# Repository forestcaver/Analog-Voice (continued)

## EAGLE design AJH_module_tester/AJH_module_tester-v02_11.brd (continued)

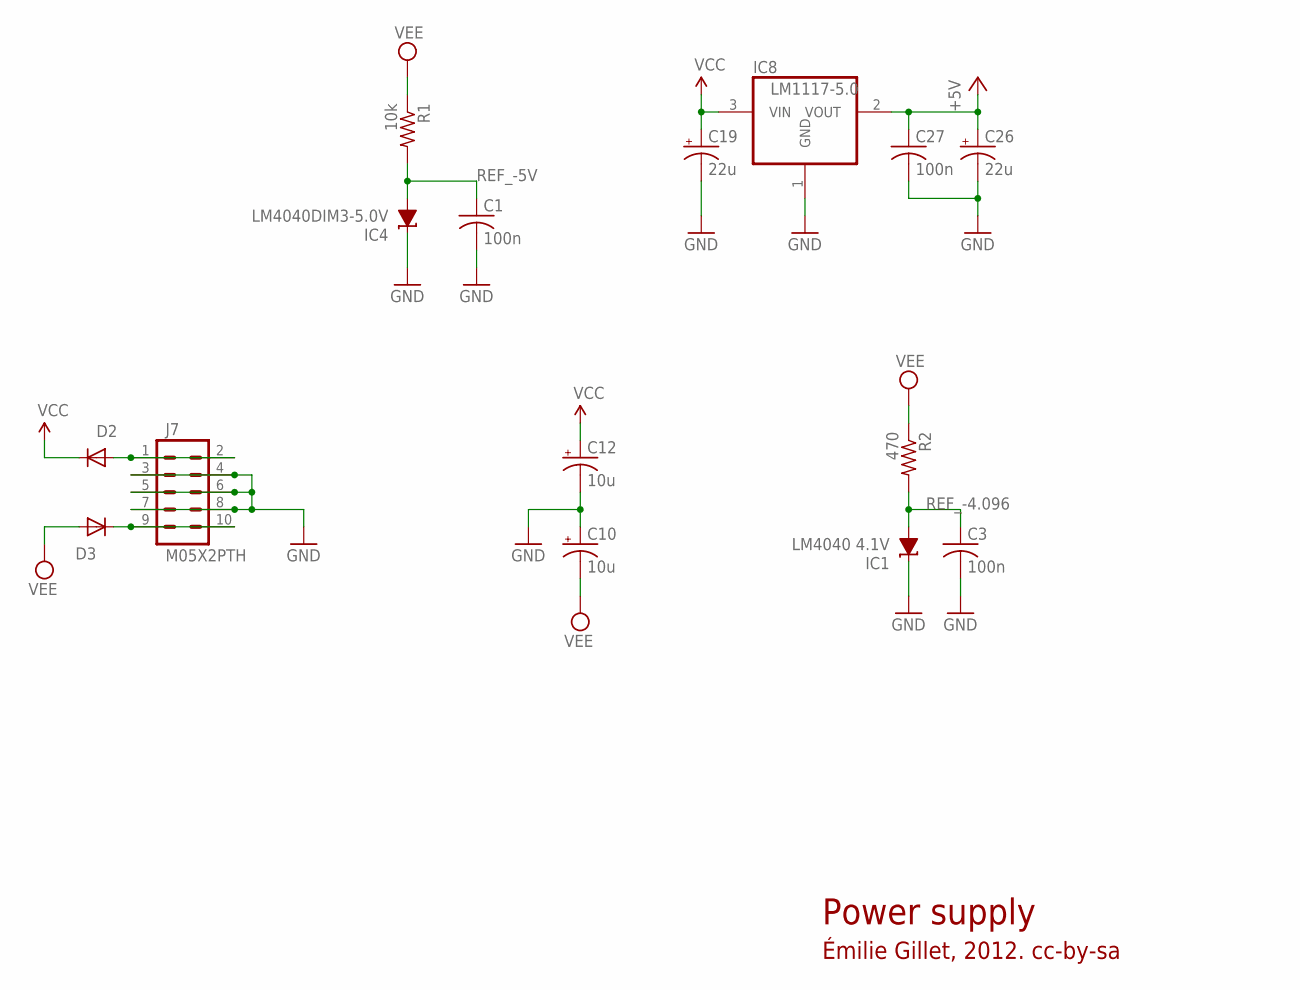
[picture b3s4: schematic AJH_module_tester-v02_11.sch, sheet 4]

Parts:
C1, C3, C27: 100n; C0603
C10, C12: 10u; PANASONIC_A
C19, C26: 22u; PANASONIC_C
D2, D3: 1N5819HW; SOD123
IC1: LM4040 4.1V; DBZ_R-PDSO-G3
IC4: LM4040DIM3-5.0V; DBZ_R-PDSO-G3
IC8: LM1117-5.0; SOT223
J7: M05X2PTH; AVR_ICSP
R1: 10k; R0603
R2: 470; R0603

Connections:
+5V: C26.+, C27.1, IC8.2 (VOUT); also elsewhere on the board
GND: C1.2, C3.2, C10.+, C12.-, C19.-, C26.-, C27.2, IC1.1 (C), IC4.1 (C), IC8.1 (GND), J7.3, J7.4, J7.5, J7.6, J7.7, J7.8; also elsewhere on the board
unnamed: D2.A, J7.1, J7.2
unnamed: D3.C, J7.9, J7.10
REF_-4.096: C3.1, IC1.2 (A), R2.2; also elsewhere on the board
REF_-5V: C1.1, IC4.2 (A), R1.2; also elsewhere on the board
VCC: C12.+, C19.+, D2.C, IC8.3 (VIN); also elsewhere on the board
VEE: C10.-, D3.A, R1.1, R2.1; also elsewhere on the board

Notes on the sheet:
Power supply
Émilie Gillet, 2012. cc-by-sa

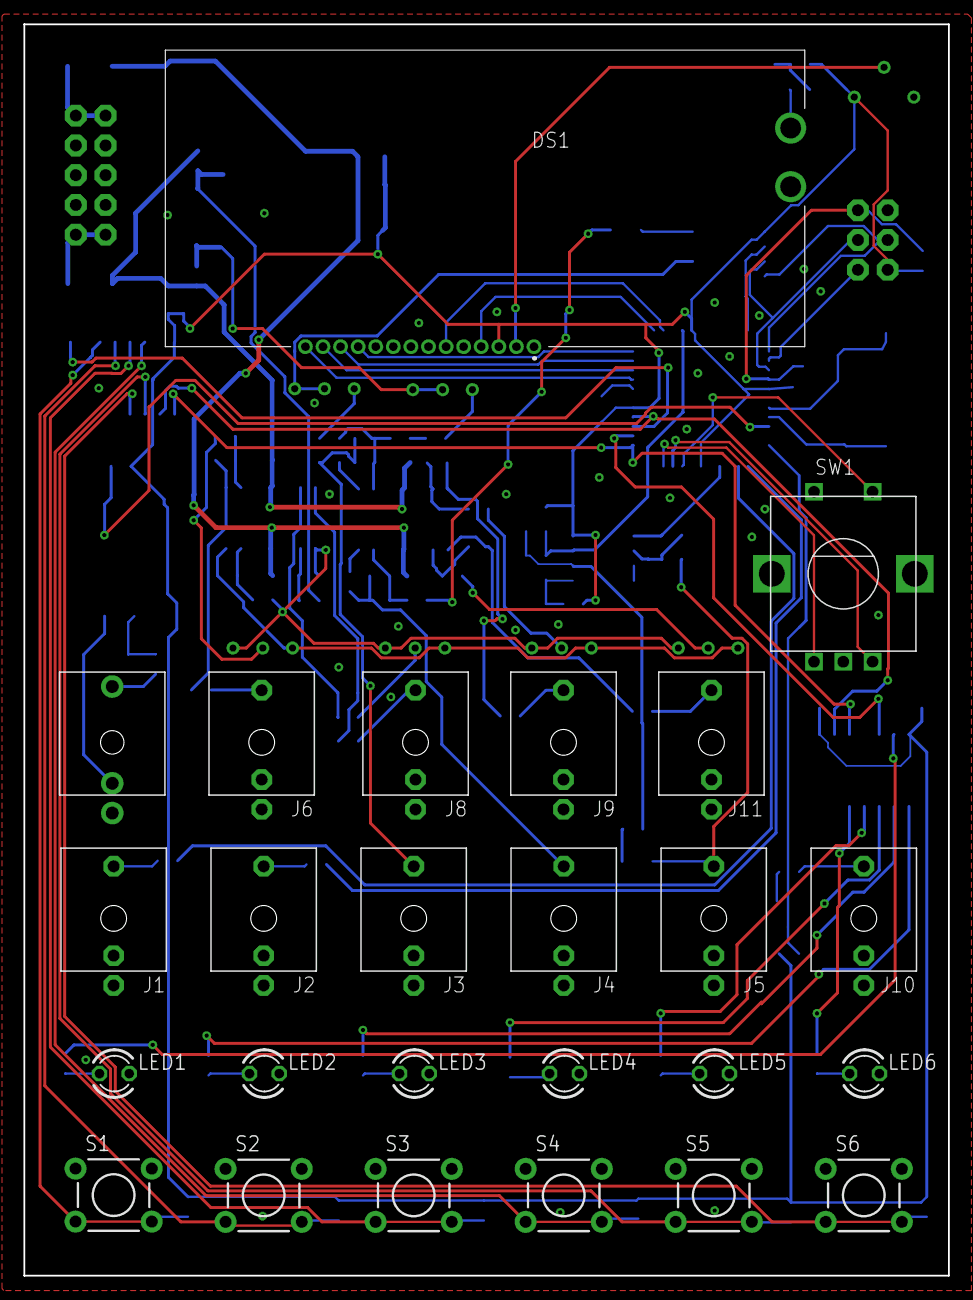
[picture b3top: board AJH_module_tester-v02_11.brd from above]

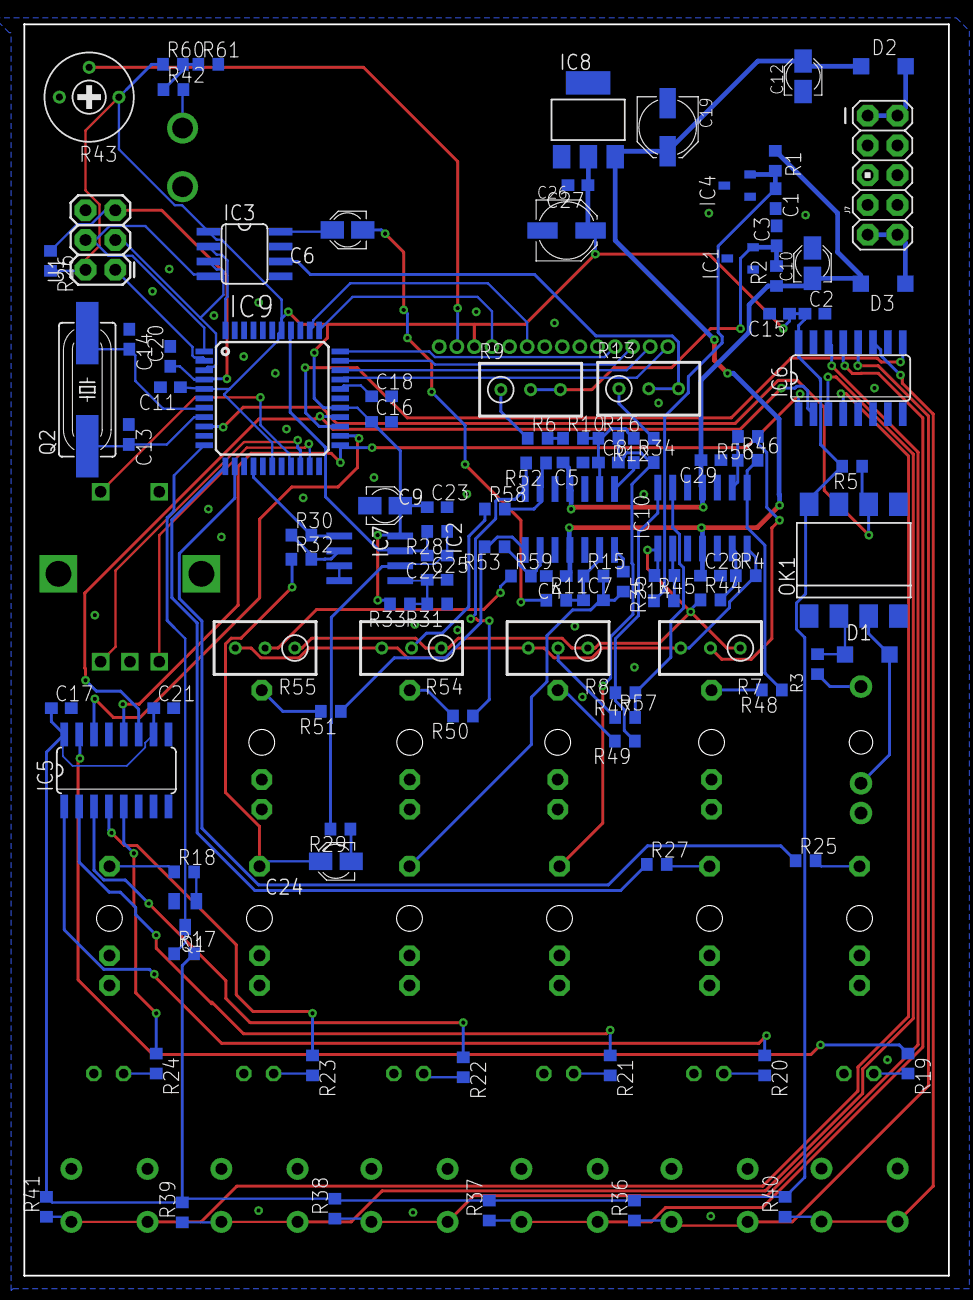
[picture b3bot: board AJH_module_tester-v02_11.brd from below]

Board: 2 copper layers, 78.9 x 106.8 mm, 133 parts (108 on the bottom side), 100 nets.
